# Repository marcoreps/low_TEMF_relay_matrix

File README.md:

# low_TEMF_relay_matrix

A low-thermal EMF relay matrix board designed for **automated 4-wire resistance measurements** and **NBS 430 voltage supervision**. Needs 5V supply and an external microcontroller to feed data into a shift register bucket brigade. Oblong terminal pads for cable shoes or brinding posts. <19" wide board for possible rack installation.

---

## Changelog

### Version 0.5
* Exposed GND copper plane around a mounting hole for convenient shield/enclosure chassis connection
* Criss-cross pattern on layers 2,3 instead of identical traces to minimize path resistance

### Version 0.4
* Symmetric annotations
* Added test points connected directly to the four buses
* Added silkscreen logos

---

## Recommended PCB

* 4 layer
* OSP (a bit difficult to strip but gives bare copper pads)
* Gold plating shouldn't be much worse

---

## Images

<div align="center">

### Overview
| 3D Render | Concept |
| :---: | :---: |
|  |  |

### Schematics
| Relay Driver | Relay Block |
| :---: | :---: |
|  |  |

### Performance
| Test Results of 0.4|
| :---: |
|  |

### Heat spreader example
| Front | Rear | Sandwitch |
| :---: | :---: | :---: |
|  |  |  |

| Taobao Terminals | 3mm Al plate | 19" width |
| :---: | :---: | :---: |
|  |  |  |

</div>

---

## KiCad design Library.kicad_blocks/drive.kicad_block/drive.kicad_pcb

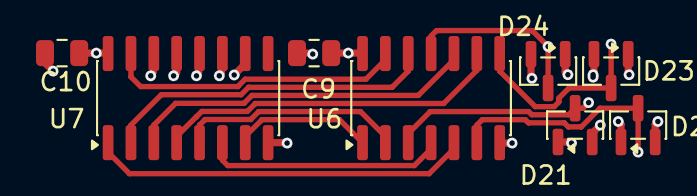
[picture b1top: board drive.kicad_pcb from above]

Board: 4 copper layers, 8 parts (0 on the bottom side), 14 nets.

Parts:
C9, C10: 100nF; C_0805_2012Metric
D21, D22, D23, D24: BAV99; SOT-23
U6: 74AC125; SOIC-14_3.9x8.7mm_P1.27mm
U7: 74HC595; SOIC-16_3.9x9.9mm_P1.27mm

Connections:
+3.3V: C9.2, C10.2, D21.2 (A), D22.2 (A), D23.2 (A), D24.2 (A), U6.14 (VCC), U7.10 (~SRCLR), U7.16 (VCC)
/inputs6/coil_row1: D22.3 (K), U6.6
/inputs6/coil_row2: D21.3 (K), U6.3
/inputs6/coil_row3: D23.3 (K), U6.8
/inputs6/coil_row4: D24.3 (K), U6.11
GND: C9.1, C10.1, D21.1 (K), D22.1 (K), D23.1 (K), D24.1 (K), U6.7 (GND), U7.8 (GND), U7.13 (~OE)
unnamed: U6.13, U7.15 (QA)
unnamed: U6.5, U7.1 (QB)
unnamed: U6.12, U7.2 (QC)
unnamed: U6.10, U7.3 (QD)
unnamed: U6.9, U7.4 (QE)
unnamed: U6.2, U7.5 (QF)
unnamed: U6.4, U7.6 (QG)
unnamed: U6.1, U7.7 (QH)

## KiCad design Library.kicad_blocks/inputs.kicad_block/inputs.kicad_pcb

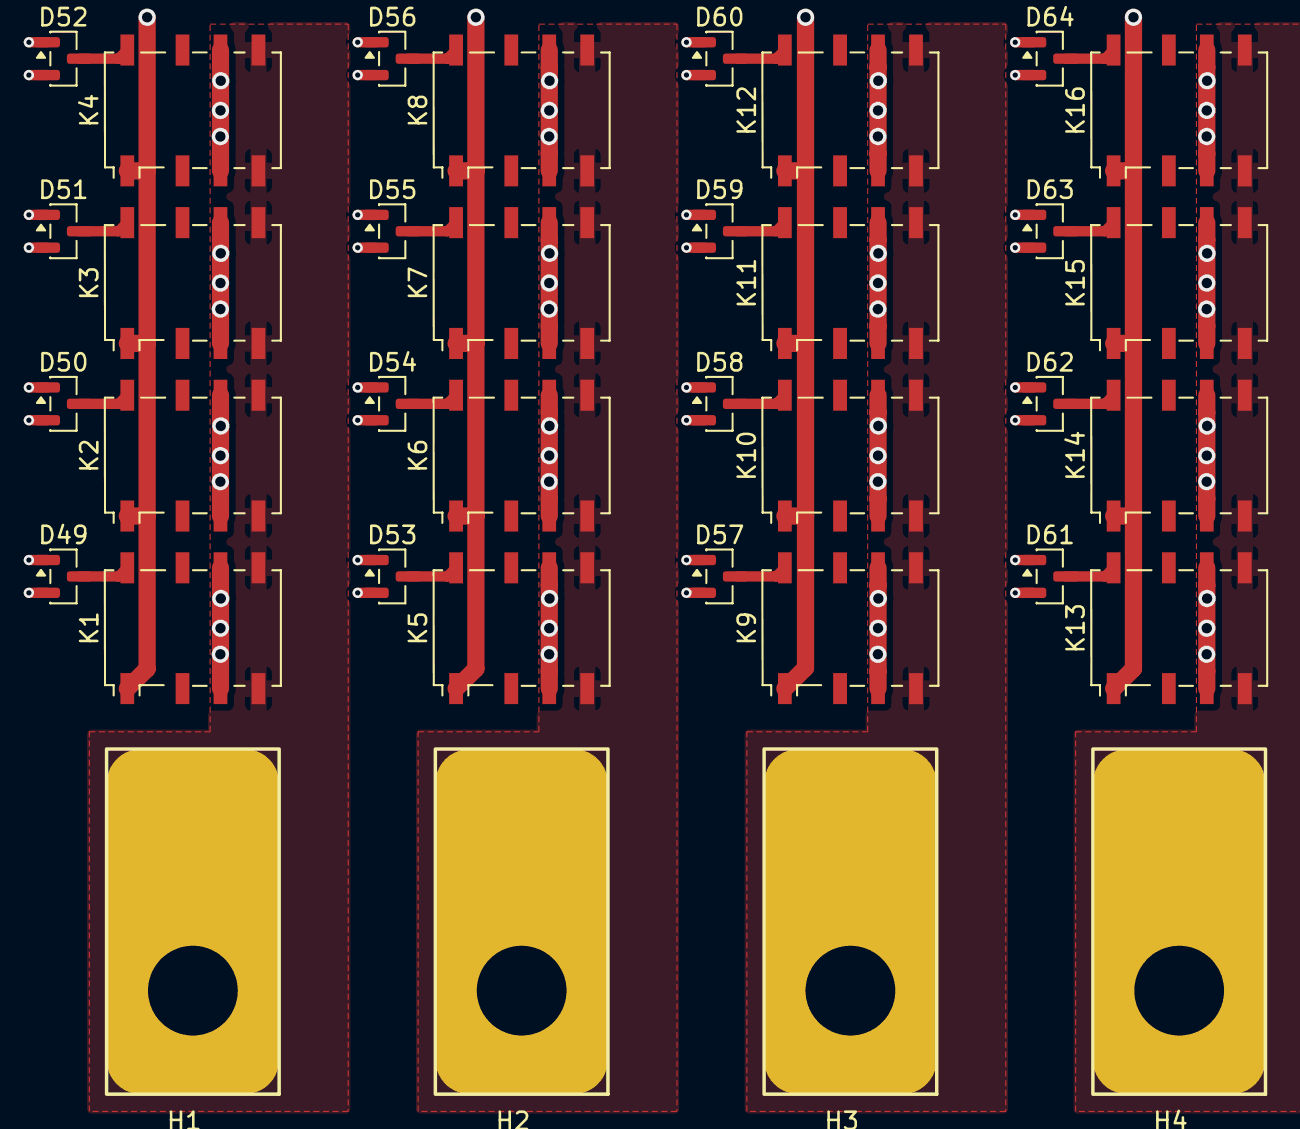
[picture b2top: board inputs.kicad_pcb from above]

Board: 4 copper layers, 36 parts (0 on the bottom side), 36 nets.

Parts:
D49, D50, D51, D52, D53, D54, D55, D56, D57, D58, D59, D60, D61, D62, D63, D64: BAV99; SOT-23
H1, H2, H3, H4: MountingHole_Pad; MountingHole_large_Pad
K1, K2, K3, K4, K5, K6, K7, K8, K9, K10, K11, K12, K13, K14, K15, K16: G6KU-2; Relay_DPDT_Omron_G6K-2F-Y

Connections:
/inputs1/coil_colA+: D49.1 (K), D53.1 (K), D57.1 (K), D61.1 (K)
/inputs1/coil_colA-: D49.2 (A), D53.2 (A), D57.2 (A), D61.2 (A)
/inputs1/coil_colB+: D50.1 (K), D54.1 (K), D58.1 (K), D62.1 (K)
/inputs1/coil_colB-: D50.2 (A), D54.2 (A), D58.2 (A), D62.2 (A)
/inputs1/coil_colC+: D51.1 (K), D55.1 (K), D59.1 (K), D63.1 (K)
/inputs1/coil_colC-: D51.2 (A), D55.2 (A), D59.2 (A), D63.2 (A)
/inputs1/coil_colD+: D52.1 (K), D56.1 (K), D60.1 (K), D64.1 (K)
/inputs1/coil_colD-: D52.2 (A), D56.2 (A), D60.2 (A), D64.2 (A)
/inputs1/coil_row1: K1.1, K2.1, K3.1, K4.1
/inputs1/coil_row2: K5.1, K6.1, K7.1, K8.1
/inputs1/coil_row3: K9.1, K10.1, K11.1, K12.1
/inputs1/coil_row4: K13.1, K14.1, K15.1, K16.1
unnamed: D49.3 (K), K1.8
unnamed: D50.3 (K), K2.8
unnamed: D51.3 (K), K3.8
unnamed: D52.3 (K), K4.8
unnamed: D53.3 (K), K5.8
unnamed: D54.3 (K), K6.8
unnamed: D55.3 (K), K7.8
unnamed: D56.3 (K), K8.8
unnamed: D57.3 (K), K9.8
unnamed: D58.3 (K), K10.8
unnamed: D59.3 (K), K11.8
unnamed: D60.3 (K), K12.8
unnamed: D61.3 (K), K13.8
unnamed: D62.3 (K), K14.8
unnamed: D63.3 (K), K15.8
unnamed: D64.3 (K), K16.8
unnamed: H1.1 (1_1), K1.4, K1.5, K2.4, K2.5, K3.4, K3.5, K4.4, K4.5
unnamed: H2.1 (1_1), K5.4, K5.5, K6.4, K6.5, K7.4, K7.5, K8.4, K8.5
unnamed: H3.1 (1_1), K9.4, K9.5, K10.4, K10.5, K11.4, K11.5, K12.4, K12.5
unnamed: H4.1 (1_1), K13.4, K13.5, K14.4, K14.5, K15.4, K15.5, K16.4, K16.5
bus_A: K1.3, K1.6, K5.3, K5.6, K9.3, K9.6, K13.3, K13.6
bus_B: K2.3, K2.6, K6.3, K6.6, K10.3, K10.6, K14.3, K14.6
bus_C: K3.3, K3.6, K7.3, K7.6, K11.3, K11.6, K15.3, K15.6
bus_D: K4.3, K4.6, K8.3, K8.6, K12.3, K12.6, K16.3, K16.6

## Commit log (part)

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2026-06-30 improved annotations
2026-06-30 Added bus test points
2026-06-30 asdf
2026-06-30 addes esp32c3 firmware
